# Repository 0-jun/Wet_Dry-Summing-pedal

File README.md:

# Wet_Dry-Summing-pedal
Effect pedals that sum dry and wet signals

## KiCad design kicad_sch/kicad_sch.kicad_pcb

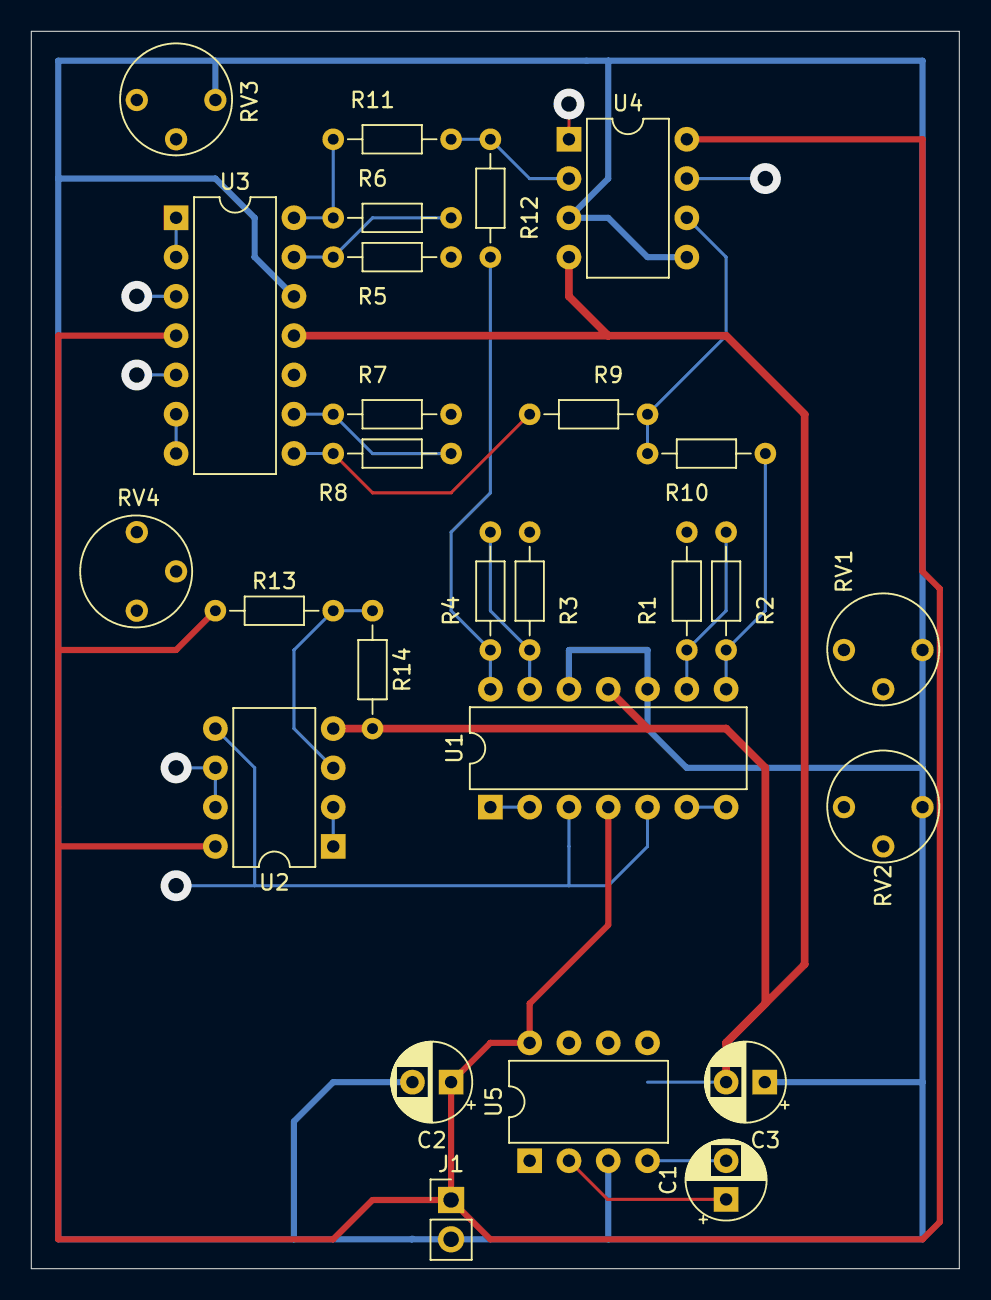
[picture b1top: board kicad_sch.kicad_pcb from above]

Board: 2 copper layers, 60.0 x 80.0 mm, 27 parts (0 on the bottom side), 27 nets.

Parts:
C1, C2, C3: C_Polarized_US; CP_Radial_D5.0mm_P2.50mm
J1: Conn_01x02; PinHeader_1x02_P2.54mm_Vertical
R1, R2, R3, R4, R5, R6, R7, R8, R9, R10, R11, R12, R13, R14: R_US; R_Axial_DIN0204_L3.6mm_D1.6mm_P7.62mm_Horizontal
RV1, RV2, RV3, RV4: R_Potentiometer_US; Potentiometer_Vishay_T7-YA_Single_Vertical
U1, U3: TL074; DIP-14_W7.62mm
U2, U4: TL072; DIP-8_W7.62mm
U5: LT1054; DIP-8_W7.62mm

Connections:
+9V: C2.1, J1.1, R13.1, U1.4 (V+), U2.8 (V+), U3.4 (V+), U4.8 (V+), U5.8 (V+)
-8V: C3.2, R14.2, U1.11 (V-), U2.4 (V-), U3.11 (V-), U4.4 (V-), U5.5 (-VOUT)
/Dry1: R2.1, R10.2, U1.8
/Dry2: R4.1, R12.2, U1.14
/Dry_Buffered_Bypass: U2.6 (-), U2.7
/Dry_In: U1.3 (+), U1.5 (+), U2.5 (+)
/WetL_Inv: R8.1, R9.2, U3.8
/WetR_Inv: R6.1, R11.2, U3.14
GND: C2.2, C3.1, J1.2, RV1.3, RV2.3, RV3.3, RV4.3, U1.10 (+), U1.12 (+), U3.10 (+), U3.12 (+), U4.3 (+), U4.5 (+), U5.3 (GND)
unnamed: R1.2, RV2.2
unnamed: R3.2, RV1.2
unnamed: R5.2, RV3.2
unnamed: R7.2, RV4.2
unnamed: RV1.1, U1.1, U1.2 (-)
unnamed: RV2.1, U1.6 (-), U1.7
unnamed: R1.1, R2.2, U1.9 (-)
unnamed: R3.1, R4.2, U1.13 (-)
unnamed: R13.2, R14.1, U2.3 (+)
unnamed: U2.1, U2.2 (-)
unnamed: RV3.1, U3.1, U3.2 (-)
unnamed: RV4.1, U3.6 (-), U3.7
unnamed: R7.1, R8.2, U3.9 (-)
unnamed: R5.1, R6.2, U3.13 (-)
unnamed: R11.1, R12.1, U4.2 (-)
unnamed: R9.1, R10.1, U4.6 (-)
unnamed: C1.1, U5.2 (CAP+)
unnamed: C1.2, U5.4 (CAP-)

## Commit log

2025-03-03 Back up: initial design (using TL07x OPAMP)
2025-03-10 Update schematic and artwork file
